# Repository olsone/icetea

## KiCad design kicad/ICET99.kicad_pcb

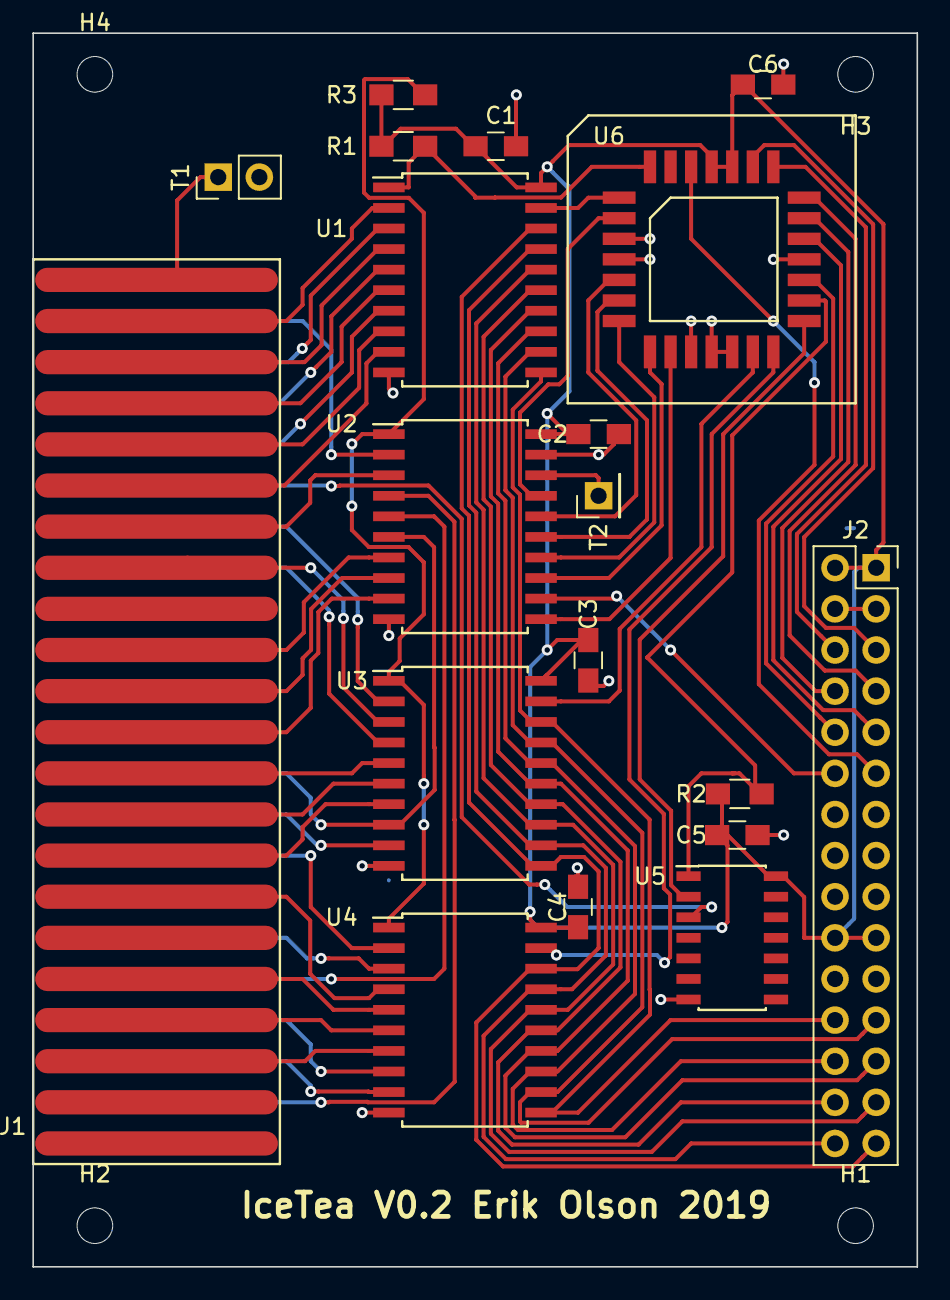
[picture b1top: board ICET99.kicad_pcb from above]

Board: 2 copper layers, 54.6 x 76.2 mm, 23 parts (0 on the bottom side), 65 nets.

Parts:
C1, C2, C3, C4, C5, C6: .1uF; C_0805_HandSoldering
H1, H2, H3, H4: MountingHole; MountingHole_2.2mm_M2
J1: Conn_02x22_Odd_Even; Card_Edge_2x22
J2: MxMod-Device; Socket_Strip_Straight_2x15_Pitch2.54mm
R1, R2, R3: 3.3K; R_0805_HandSoldering
T1: Conn_01x02; Pin_Header_Straight_1x02_Pitch2.54mm
T2: Conn_01x02; Pin_Header_Straight_1x01_Pitch2.54mm
U1, U2, U3, U4: 74LVC245A; SOIC-20W_7.5x12.8mm_Pitch1.27mm
U5: 74HCT125; SOIC-14_3.9x8.7mm_Pitch1.27mm
U6: ATF22LV10C-28J; PLCC-28

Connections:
+3V3: C1.1, C2.1, C3.1, C4.1, C5.1, C6.1, J2.1, J2.2, J2.19, J2.20, R1.2, R2.1, R3.2, U1.20, U2.20, U3.20, U4.20, U5.14, U6.1, U6.28
/A0: J1.31, U3.2
/A1: J1.30, U3.3
/A2: J1.20, U3.5
/A3: J1.10, U4.5
/A4: J1.7, U4.8
/A5: J1.5, U4.9
/A6: J1.29, U3.4
/A7: J1.17, U3.9
/A8: J1.14, U4.4
/A9: J1.18, U3.6
/A10: J1.6, U4.7
/A11: J1.8, U4.6
/A12: J1.11, U4.3
/A13: J1.15, U4.2
/A14: J1.16, U3.7
/A15CRUOUT: J1.19, U2.6, U3.8
/ABEN1: U3.19, U6.17
/ABEN2: U4.19, U6.18
/AUDIOIN: J1.44, T1.1
/BA15CRUOUT: U2.14, U6.11
/BCRUCLK: U2.11, U6.13
/BD0: J2.28, U1.15, U3.14, U4.15
/BD1: J2.27, U1.16, U3.13, U4.16
/BD2: J2.30, U1.17, U3.12, U4.17
/BD3: J2.29, U1.18, U3.11, U4.18
/BD4: J2.26, U1.13, U3.16, U4.13
/BD5: J2.25, U1.14, U3.15, U4.14
/BD6: J2.23, U1.12, U3.17, U4.12
/BD7: J2.24, U1.11, U3.18, U4.11
/BDBIN: U2.15, U6.10
/BIAQ: T2.1, U2.18
/BMEMEN*: U2.17, U6.6
/BPHI3*: J2.12, U2.12
/BRESET*: U2.16, U6.9
/BWE*: U2.13, U6.12
/CLKIN: J2.11, U6.2
/CRUBIT: U5.2, U6.19
/CRUCLK: J1.22, U2.9
/CRUEN: R2.2, U5.1, U6.20
/CRUIN: J1.33, U5.3
/D0: J1.37, U1.5
/D1: J1.40, U1.4
/D2: J1.39, U1.3
/D3: J1.42, U1.2
/D4: J1.35, U1.7
/D5: J1.38, U1.6
/D6: J1.36, U1.8
/D7: J1.34, U1.9
/DBDIR: R1.1, U1.1, U6.4
/DBEN1: U1.19, U6.5
/DBIN: J1.9, U2.5
/DEC0: J2.8, U6.24
/DEC1: J2.9, U6.23
/DEC2: J2.10, U6.21
/ENC0: J2.7, U6.25
/ENC1: J2.6, U6.26
/ENC2: J2.5, U6.27
/IAQ: J1.41, U2.2
/MEMEN*: J1.32, U2.3
/PHI3*: J1.24, U2.8
/RESET*: J1.3, U2.4
/WE*: J1.26, U2.7
GND: C1.2, C2.2, C3.2, C4.2, C5.2, C6.2, J1.21, J1.23, J1.25, J1.27, J2.3, J2.4, J2.21, J2.22, T1.2, U1.10, U2.10, U2.19, U3.10, U4.10, U5.7, U6.7, U6.8, U6.14, U6.15, U6.16, U6.22
unnamed: R3.1, U2.1, U3.1, U4.1

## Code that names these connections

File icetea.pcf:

###############################################################################
#                                                                             #
# Copyright 2017 myStorm Copyright and related                                #
# rights are licensed under the Solderpad Hardware License, Version 0.51      #
# (the “License”); you may not use this file except in compliance with        #
# the License. You may obtain a copy of the License at                        #
# http://solderpad.org/licenses/SHL-0.51. Unless required by applicable       #
# law or agreed to in writing, software, hardware and materials               #
# distributed under this License is distributed on an “AS IS” BASIS,          #
# WITHOUT WARRANTIES OR CONDITIONS OF ANY KIND, either express or             #
# implied. See the License for the specific language governing                #
# permissions and limitations under the License.                              #
#                                                                             #
###############################################################################

# User Constraint File for myStorm BlackIce II   - Ken Boak   09-12-17

#pmod 1 (Uart pmod)
set_io PMOD[0] 94 # rd6
set_io PMOD[1] 91 # rd4 shared with RTS and pin 128 see below
set_io PMOD[2] 88 # rd2
set_io PMOD[3] 85 # rd0

#pmod 2
set_io PMOD[4] 95 # rd7
set_io PMOD[5] 93 # rd5
set_io PMOD[6] 90 # rd3
set_io PMOD[7] 87 # rd1

#pmod 3 GPIO
set_io PMOD[8] 105 # c5
set_io PMOD[9] 102 # c3
set_io PMOD[10] 99 # c1
set_io PMOD[11] 97 # i_tx

#pmod 4
set_io PMOD[12] 104 # c4
set_io PMOD[13] 101 # c2
set_io PMOD[14] 98 # c0
set_io PMOD[15] 96 # i_rx

#pmod 5 GPIO
# dig snd extra
set_io PMOD[16] 143 #g2
set_io PMOD[17] 114 #c11
set_io PMOD[18] 112 #c9
set_io PMOD[19] 107 #c7

#pmod 6 GPIO
# i2s 
set_io PMOD[20] 144 #G1
set_io PMOD[21] 113 #C10
set_io PMOD[22] 110 #C8
set_io PMOD[23] 106 #C6

#pmod 7 lvds pairs 2 & 5
set_io RDBENA   10 # 5b    o
set_io ADRIN1    9 # 5a    i
set_io SRCLK     2 # 2b    i
set_io BCRUIN    1 # 2a    o

#pmod 8 lvds pairs 3 & 4
set_io DBDIR     8 # 4b    o
set_io SHLD      7 # 4a    o
set_io ADRIN2    4 # 3b    i
set_io EN_CRUIN  3 # 3a    o

#pmod 9 lvds pairs 10 & 13
set_io BIAQ     20 # 13b   i
set_io BWE      19 # 13a   i
set_io BCRUCLK  16 # 10b   i
set_io BDBIN    15 # 10a   i

#pmod 10 lvds pairs 8 & 12
set_io BMEMEN   18 # 12b   i
set_io BPHI3    17 # 12a   i
set_io BCRUOUT  12 # 8b    i
set_io BRESET   11 # 8a    i


#pmod 11 lvds pairs 14 & 25
set_io BDB[4]   34 # 25b  io 
set_io BDB[6]   33 # 25a  io
set_io BDB[3]   22 # 14B  io 
set_io BDB[0]   21 # 14a  io  

#pmod 12 lvds pairs 18 & 24
set_io BDB[5]   32 # 24b  io
set_io BDB[7]   31 # 24a  io
set_io BDB[2]   26 # 18b  io
set_io BDB[1]   25 # 18a  io 

#pmod 13 DIG16-DIG19
# i2s didn't work out here. were all the switches grounded? try again
set_io PMODC[0] 37  # DIG19
set_io PMODC[1] 38  # DIG18
set_io PMODC[2] 39  # DIG17
set_io PMODC[3] 41  # DIG16

#pmod 14 SPI muxed with leds
set_io PMODC[4] 71 #LD4,!SS,p14_1
set_io PMODC[5] 67 #LD3,MISO,p14_2
set_io PMODC[6] 68 #LD2,MOSI,p14_3
set_io PMODC[7] 70 #LD1,SCL,p14_4
# Buttons
set_io B1 63 # Push Button 1
set_io B2 64 # Push Button 2#


# SRAM
set_io ADR[0] 137
set_io ADR[1] 138
set_io ADR[2] 139
set_io ADR[3] 141
set_io ADR[4] 142
set_io ADR[5] 42
set_io ADR[6] 43
set_io ADR[7] 44
set_io ADR[8] 73
set_io ADR[9] 74
set_io ADR[10] 75
set_io ADR[11] 76
set_io ADR[12] 115
set_io ADR[13] 116
set_io ADR[14] 117
set_io ADR[15] 118
set_io ADR[16] 119
set_io ADR[17] 78

set_io DAT[0] 136
set_io DAT[1] 135
set_io DAT[2] 134
set_io DAT[3] 130
set_io DAT[4] 125
set_io DAT[5] 124
set_io DAT[6] 122
set_io DAT[7] 121
set_io DAT[8] 62
set_io DAT[9] 61
set_io DAT[10] 60
set_io DAT[11] 56
set_io DAT[12] 55
set_io DAT[13] 48
set_io DAT[14] 47
set_io DAT[15] 45

set_io RAMOE 29
set_io RAMWE 120
set_io RAMCS 23
set_io RAMUB 28
set_io RAMLB 24

# QUAD SPI
set_io QSPICSN 81
set_io QSPICK 82
set_io QSPIDQ[0] 83
set_io QSPIDQ[1] 84
set_io QSPIDQ[2] 79
set_io QSPIDQ[3] 80

# Debug
set_io DONE 52 # DONE - GBIN4
set_io DBG1 49 # DBG1 - GBIN5

# Internal global reset
set_io greset 128 # Connected to CH340 RTS and also P1 (uart Pmod above)

# Onboard 100Mhz oscillator
set_io clk 129

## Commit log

2018-04-10 initial checkin
2018-04-10 added comment
2018-05-25 SweetTea schematic
2018-05-26 March2017 verilog i2s and FORTH sd card FAT32
2018-09-11 Pdf of schematic
2018-09-12 Diagrams of Hardware Use Cases
2018-10-11 working to eliminate warnings
2018-10-11 new files added toward working hardware
2018-10-11 makefile
2018-10-28 working on getting i2s up
2018-11-10 wavetable synth mostly working, address bus mostly working
2018-11-20 <# enter change notes here #>
2018-12-11 Checkpoint. Console memory cycle gives wrong page# still
2019-01-05 Memory interface returning values to 4A
2019-01-05 data bus all correct in pcf
2019-01-19 memory cycles working, with glitches
2019-05-28 PCB design for v0.2
2019-07-19 Updated schematic
